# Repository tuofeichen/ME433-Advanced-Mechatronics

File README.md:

# ME433-Advanced-Mechatronics
This is a course repo for ME 433 Advanced Mechatronics at Northwestern. In this class, I build a mobile robot that's controlled by an Android phone to follow a colored line. 

I use the camera of the phone to track the line and I use a PIC32 microcontroller to control the motor. The phone and the PIC32 communicates via USB. 

The final java code for the android phone is in TechCupAndroid folder while the final C code for the PIC32 is in the TechCupPIC folder. 

I laser cut and 3D printed all the mounting fixture (including suspension and wheels). 

See below as the final demonstration.

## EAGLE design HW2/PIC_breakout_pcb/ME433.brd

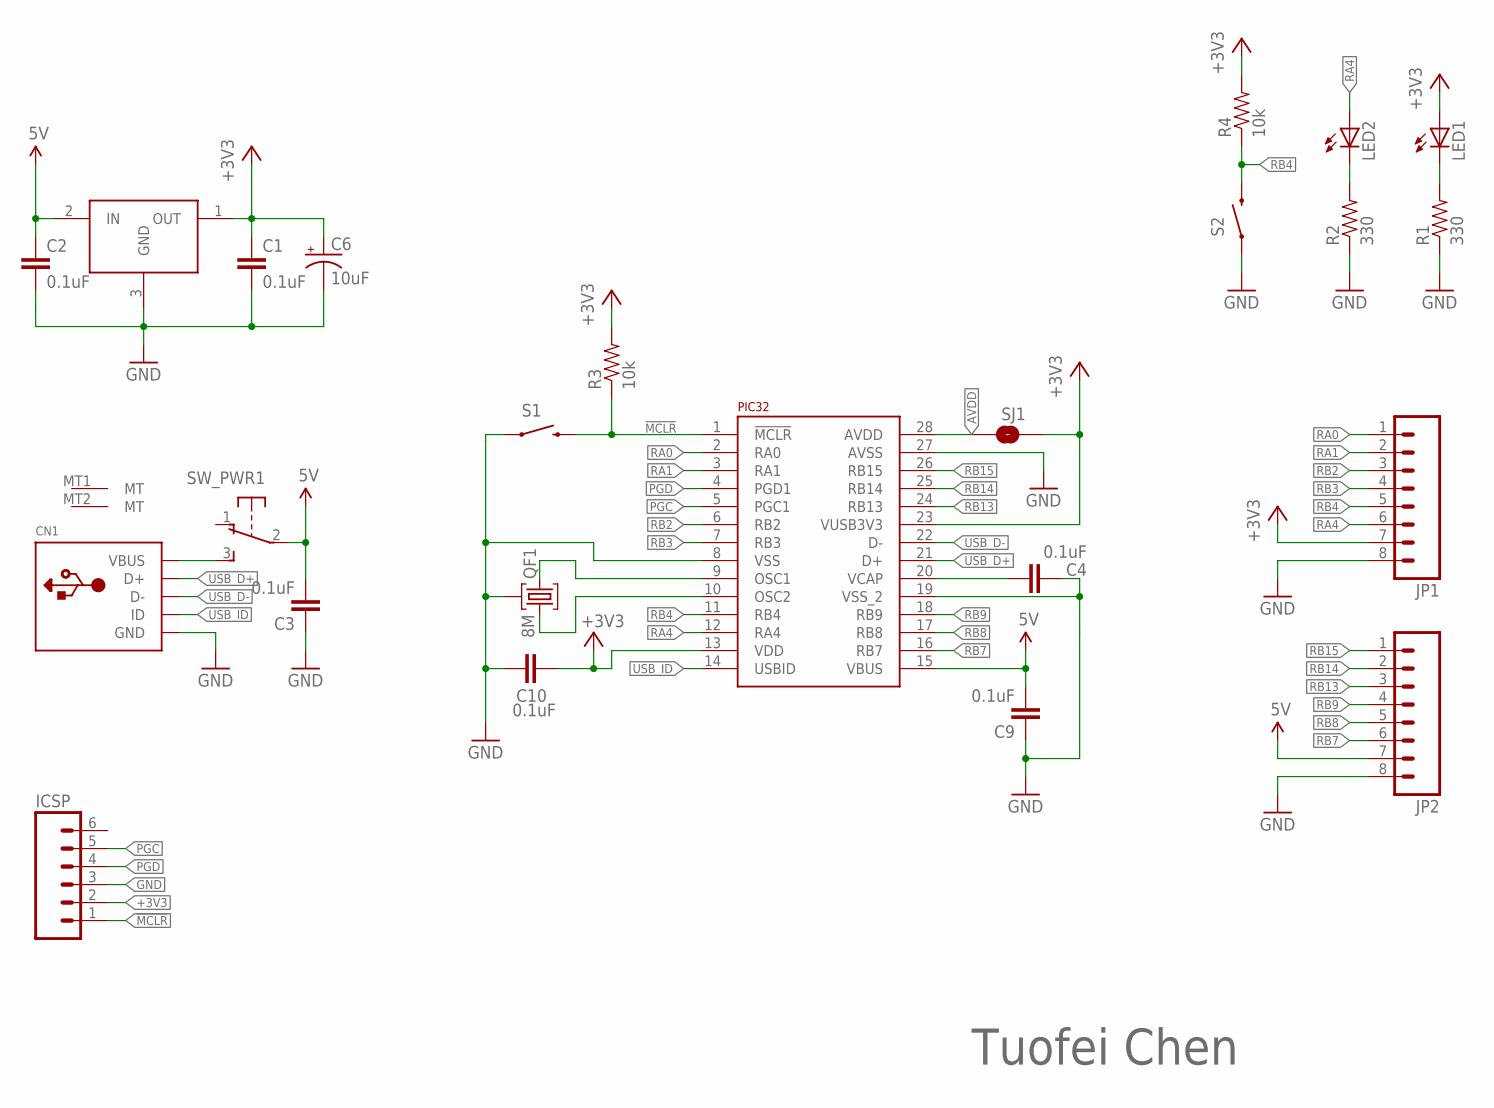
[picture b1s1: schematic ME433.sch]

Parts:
3V3-REG: 3V3-REG-TO92; TO-92
C1, C2, C3, C4, C9, C10: 0.1uF; CAP-PTH-SMALL
C6: 10uF; CPOL-RADIAL-100UF-25V
CN1: USBMOLEX; USB-MINIB-THM-MOLEX
ICSP: M06LONGPADS; 1X06_LONGPADS
JP1, JP2: M08LONGPADS; 1X08_LONGPADS
LED1, LED2: LED3MM
PIC32: PIC32MX250F128B-DIP; DIP28
QF1: 8M; HC49U
R1, R2: 330; AXIAL-0.3
R3, R4: 10k; AXIAL-0.3
S1, S2: PUSH_BUT; 1X02_LOCK_LONGPADS
SJ1: SOLDERJUMPERNC; SJ_2S
SW_PWR: EG1213

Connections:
5V: 3V3-REG.2 (IN), C2.1, C3.2, C9.2, JP2.7, PIC32.15 (VBUS), SW_PWR.2
!MCLR: ICSP.1, PIC32.1 (!MCLR), R3.P$1 (1), S1.2
+3V3: 3V3-REG.1 (OUT), C1.1, C6.1 (+), C10.2, ICSP.2, JP1.7, LED1.A, PIC32.13 (VDD), PIC32.23 (VUSB3V3), R3.P$2 (2), R4.P$2 (2), SJ1.1
AVDD: PIC32.28 (AVDD), SJ1.2
GND: 3V3-REG.3 (GND), C1.2, C2.2, C3.1, C4.2, C6.2 (-), C9.1, C10.1, CN1.GND, ICSP.3, JP1.8, JP2.8, PIC32.8 (VSS), PIC32.19 (VSS_2), PIC32.27 (AVSS), QF1.2, R1.P$1 (1), R2.P$1 (1), S1.1, S2.1
unnamed: PIC32.9 (OSC1), QF1.1
unnamed: PIC32.10 (OSC2), QF1.3
unnamed: LED2.K (C), R2.P$2 (2)
unnamed: C4.1, PIC32.20 (VCAP)
unnamed: LED1.K (C), R1.P$2 (2)
unnamed: CN1.VBUS, SW_PWR.3 (S)
PGC: ICSP.5, PIC32.5 (PGC1)
PGD: ICSP.4, PIC32.4 (PGD1)
RA0: JP1.1, PIC32.2 (RA0)
RA1: JP1.2, PIC32.3 (RA1)
RA4: JP1.6, LED2.A, PIC32.12 (RA4)
RB2: JP1.3, PIC32.6 (RB2)
RB3: JP1.4, PIC32.7 (RB3)
RB4: JP1.5, PIC32.11 (RB4), R4.P$1 (1), S2.2
RB7: JP2.6, PIC32.16 (RB7)
RB8: JP2.5, PIC32.17 (RB8)
RB9: JP2.4, PIC32.18 (RB9)
RB13: JP2.3, PIC32.24 (RB13)
RB14: JP2.2, PIC32.25 (RB14)
RB15: JP2.1, PIC32.26 (RB15)
USB_D+: CN1.D+, PIC32.21 (D+)
USB_D-: CN1.D-, PIC32.22 (D-)
USB_ID: CN1.ID, PIC32.14 (USBID)

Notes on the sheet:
Tuofei Chen

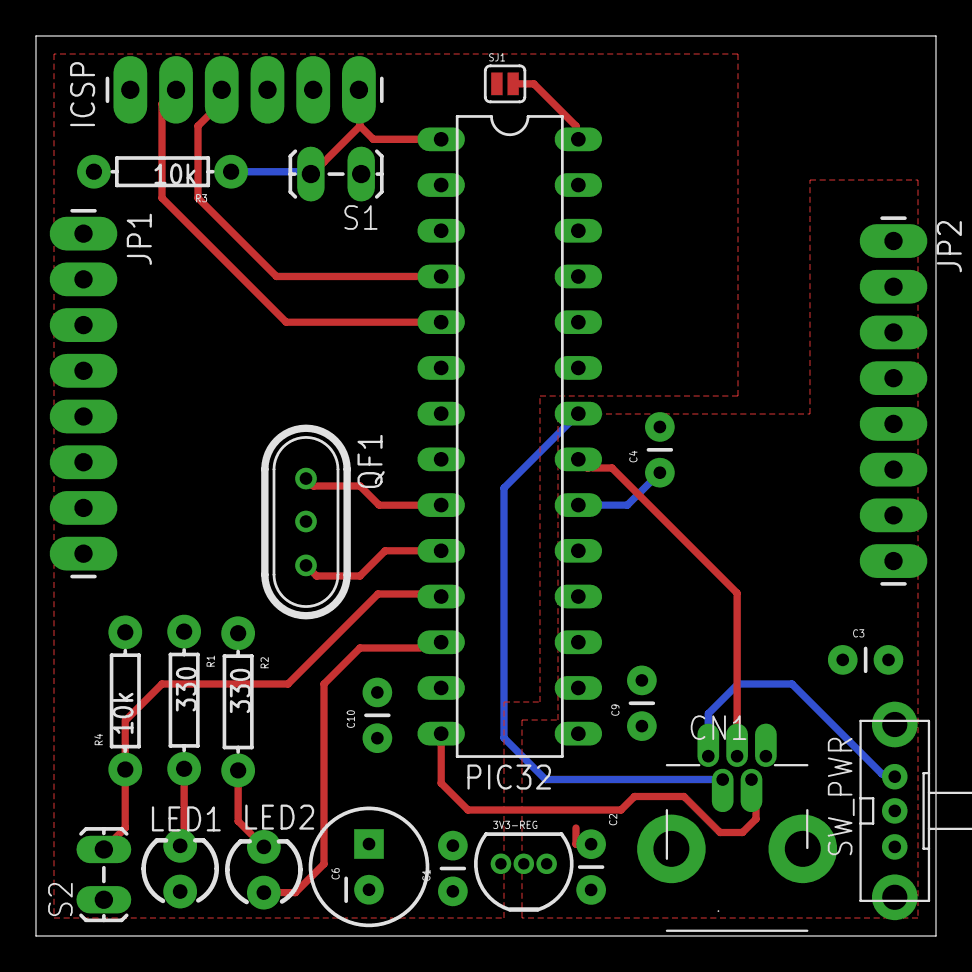
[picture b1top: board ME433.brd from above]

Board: 2 copper layers, 50.0 x 50.0 mm, 24 parts (0 on the bottom side), 28 nets.

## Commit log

2017-03-29 HW1 code
2017-03-29 new gitignore and images
2017-03-29 rename files
2017-03-30 images
2017-04-01 add pcb, update gitignore file
2017-04-05 add gerber file for pic breakout
2017-04-05 modify gitignore, add new cam file
2017-04-05 add final board file
2017-04-07 hw 4 code
2017-04-07 waveform image, change waveform frequency
2017-04-09 circuit diagram
2017-04-11 switch to timer interrupt for the timing
2017-04-12 i2c blinker hw5
2017-04-13 remove unnecessary file
2017-04-14 hw 6 lcd code
2017-04-14 fixed frequency
2017-04-16 fixed clear progress bar
2017-04-18 fix hw6 clear interrupt flag in isr
2017-04-20 imu screen code
2017-04-20 hw 7 video;
2017-04-20 harmoney version of hw7
2017-04-20 revised gitignore file
2017-04-20 remove project files
2017-04-20 add back in git project files
2017-04-20 makefile for projects
2017-04-20 hw 8 reupload
2017-04-24 clean up imu code
2017-04-25 harmony usb comm
2017-04-27 polish state machine to also echo back key press
2017-04-27 spi debug
2017-04-27 add dsp filters
2017-04-27 add filtered log
2017-05-01 add matlab utility for fft and some log data for imu output
2017-05-01 add imu plot
2017-05-02 imu based mouse
2017-05-02 refresh speed and mouse button
2017-05-04 android hello world
2017-05-04 new gitignore
2017-05-04 java program for progress bars
2017-05-11 HW13 Android Camera
2017-05-11 HW14 Android USB code
2017-05-11 hw 14 pic code
2017-05-15 hw 14 usb code
2017-05-20 add cad and wheel
2017-05-25 add laser cut box
2017-05-30 following the line
2017-06-03 add motor control code
2017-06-07 tech up final code
2017-06-07 rename
2017-06-07 add vive code, fine tune controller
2017-06-09 final code

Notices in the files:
parts and their libraries:
SparkFun-Capacitors: Licensing: Creative Commons ShareAlike 4.0 International - https://creativecommons.org/licenses/by-sa/4.0
